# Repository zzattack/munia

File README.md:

MUNIA is a device that acquires input packets from controllers of various videogame consoles and shows them on your PC with the controller simultaneously remaining attached to its console. This allows you to display your inputs on gameplay videos or livestream content.
Devices for several consoles have been developed under this project:
* Nintendo Gamecube
* Sony Playstation 2
* Nintendo 64
* Super Nintendo

# Repository overview
* The hardware folder contains schematics for the various devices developed under this project. These include input adapters for Nintendo Gamecube, Nintendo 64, Super Nintendo, Sony PlayStation 2 and hybrids of the aforementioned.
* The firmware folder contains firmware projects for each of the circuit boards presented in the hardware folder.
* The munia.io folder contains the Django project powering the http://munia.io website (not functional).
* The MUNIA-win folder contains the .NET project 

## FAQ
Q. I don’t like the default skins, can I change them?
Absolutely. The software has a very strong SVG based theming engine. You can create a new one using tools like Adobe Illustrator or Inkscape. Custom XML attributes are used to map buttons to graphical elements. It’s pretty simple, honestly; take a look in SKINS.md!

Q. What does ‘MUNIA’ mean?
The very first iteration of the device supported SNES, N64 and NGC simultaneously. The acronym stands for ‘Multi-use Nintendo Input Adapter’. Both the Multi-use and Nintendo parts no longer apply to most of our devices, so we’ve parted with the acronym but kept the pretty name.

Q. Will you support console ‘X’?
Unless mentioned on the index page, the likely answer is no. Newer generation consoles are usually too complicated. The low expected demand for adapters for older generation consoles doesn’t warrant the required development investments at the moment.

Q. How does this compare to an Arduino input display?
Favorably. Benefits include not having to splice any cables, the device showing up as HID device on your computer, superior software, more stable firmware, ability to use the controller on our PC in e.g. emulators and better 3rd party controller support. In the end, though, both work and the MUNIA software also supports inputs from Arduino-based NintendoSpy devices!

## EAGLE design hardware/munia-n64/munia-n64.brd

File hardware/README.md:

# This folder contains the EAGLE schematics for the various hardware boards.

## munia
This contains schematics and board layout for the 3-in-1 device with support for the Nintendo Gamecube, Nintendo 64 and Super Nintendo/SFC consoles.
The enclosure also makes use of the 

## munia-ngc
This is the simplified Gamecube-only version of the device

## munia-n64
This is the simplified N64-only version of the device

## munia-snes
This is the simplified SNES-only version of the device

## musia
This is the Sony PS2 version

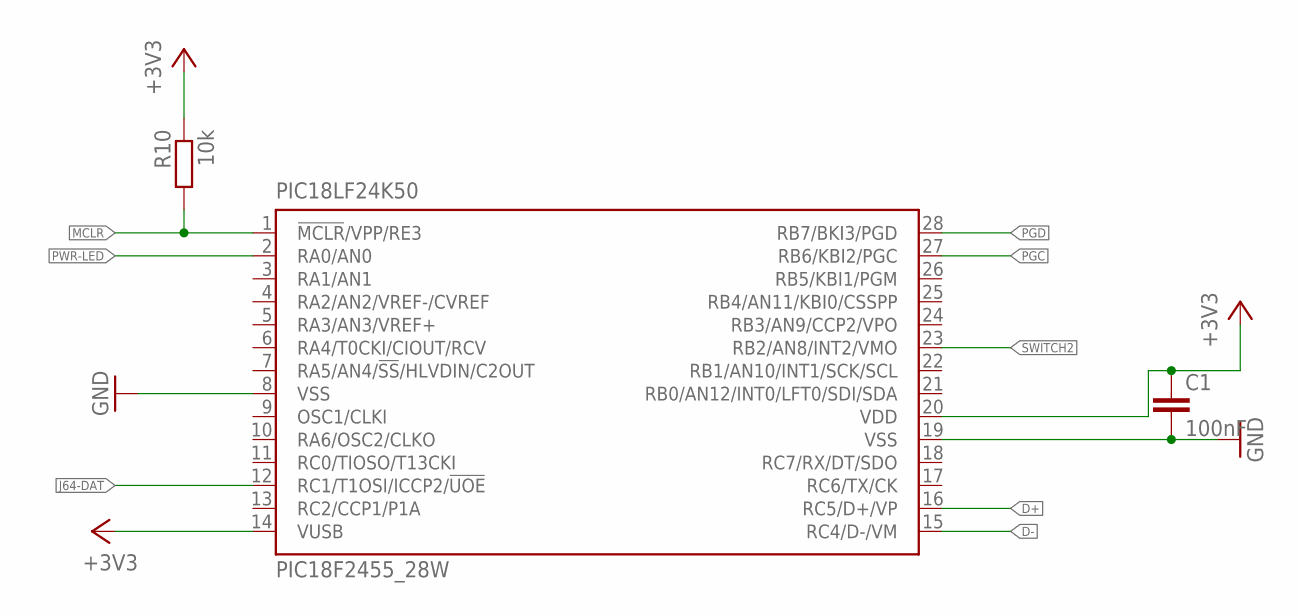
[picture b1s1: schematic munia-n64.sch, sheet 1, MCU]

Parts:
C1: 100nF; C0603
PIC18LF24K50: PIC18F2455_28W; SO28W
R10: 10k; R0603

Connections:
+3V3: C1.1, PIC18LF24K50.14 (VUSB), PIC18LF24K50.20 (VDD), R10.1; also elsewhere on the board
D+: PIC18LF24K50.16 (RC5/D+/VP); also elsewhere on the board
D-: PIC18LF24K50.15 (RC4/D-/VM); also elsewhere on the board
GND: C1.2, PIC18LF24K50.8 (VSS), PIC18LF24K50.19 (VSS); also elsewhere on the board
J64-DAT: PIC18LF24K50.12 (RC1/T1OSI/ICCP2/!UOE); also elsewhere on the board
MCLR: PIC18LF24K50.1 (!MCLR!/VPP/RE3), R10.2; also elsewhere on the board
PGC: PIC18LF24K50.27 (RB6/KBI2/PGC); also elsewhere on the board
PGD: PIC18LF24K50.28 (RB7/BKI3/PGD); also elsewhere on the board
PWR-LED: PIC18LF24K50.2 (RA0/AN0); also elsewhere on the board
SWITCH2: PIC18LF24K50.23 (RB2/AN8/INT2/VMO)

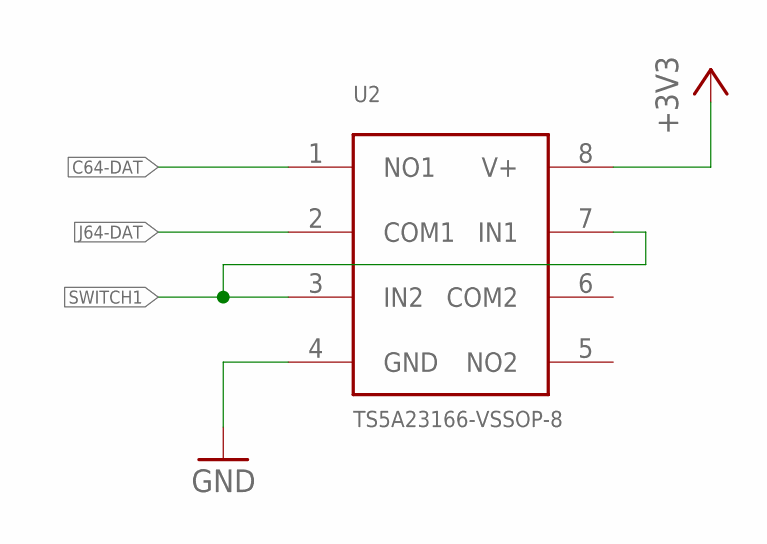
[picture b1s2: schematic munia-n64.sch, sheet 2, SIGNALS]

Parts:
U2: TS5A23166-VSSOP-8; SOT765

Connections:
+3V3: U2.8 (V+); also elsewhere on the board
C64-DAT: U2.1 (NO1); also elsewhere on the board
GND: U2.4 (GND); also elsewhere on the board
J64-DAT: U2.2 (COM1); also elsewhere on the board
SWITCH1: U2.3 (IN2), U2.7 (IN1)

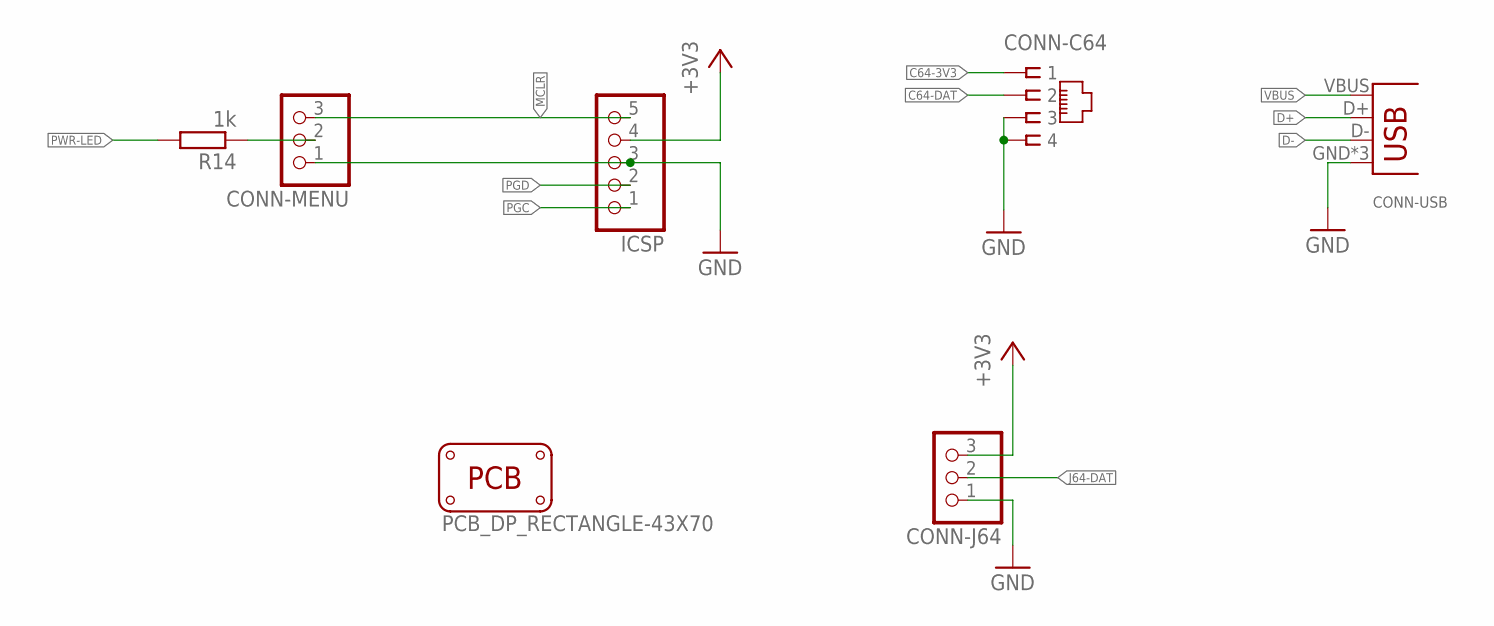
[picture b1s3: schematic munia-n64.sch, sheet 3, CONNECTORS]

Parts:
CONN-C64: RJ11-6P4C; RJ11-4C
CONN-J64: PINHD-1X3; 1X03
CONN-MENU: PINHD-1X3; 1X03
CONN-USB: USB-B-NIELS; USB-B-H
ICSP: PINHD-1X5; 1X05
PCB1: PCB_DP_RECTANGLE-43X70; DP7043_V1
R14: 1k; R0603

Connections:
+3V3: CONN-J64.3, ICSP.4; also elsewhere on the board
C64-3V3: CONN-C64.1; also elsewhere on the board
C64-DAT: CONN-C64.2; also elsewhere on the board
D+: CONN-USB.D+; also elsewhere on the board
D-: CONN-USB.D-; also elsewhere on the board
GND: CONN-C64.3, CONN-C64.4, CONN-J64.1, CONN-MENU.1, CONN-USB.GND, CONN-USB.GND@1 (GND), CONN-USB.GND@2 (GND), ICSP.3; also elsewhere on the board
J64-DAT: CONN-J64.2; also elsewhere on the board
MCLR: CONN-MENU.3, ICSP.5; also elsewhere on the board
unnamed: CONN-MENU.2, R14.1
PGC: ICSP.1; also elsewhere on the board
PGD: ICSP.2; also elsewhere on the board
PWR-LED: R14.2; also elsewhere on the board
VBUS: CONN-USB.VBUS; also elsewhere on the board

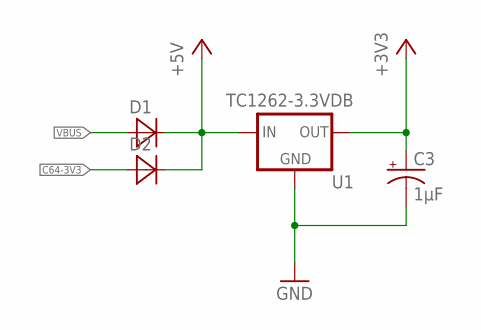
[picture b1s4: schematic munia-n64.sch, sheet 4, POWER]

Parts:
C3: 1µF; EIA3216
D1, D2: MBR120VLSFT1G; SOD123
U1: TC1262-3.3VDB; SOT230P700X180-4N

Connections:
+3V3: C3.A (+), U1.3 (OUT); also elsewhere on the board
+5V: D1.1 (C), D2.1 (C), U1.1 (IN)
C64-3V3: D2.2 (A); also elsewhere on the board
GND: C3.C (-), U1.2 (GND), U1.4 (GND); also elsewhere on the board
VBUS: D1.2 (A); also elsewhere on the board

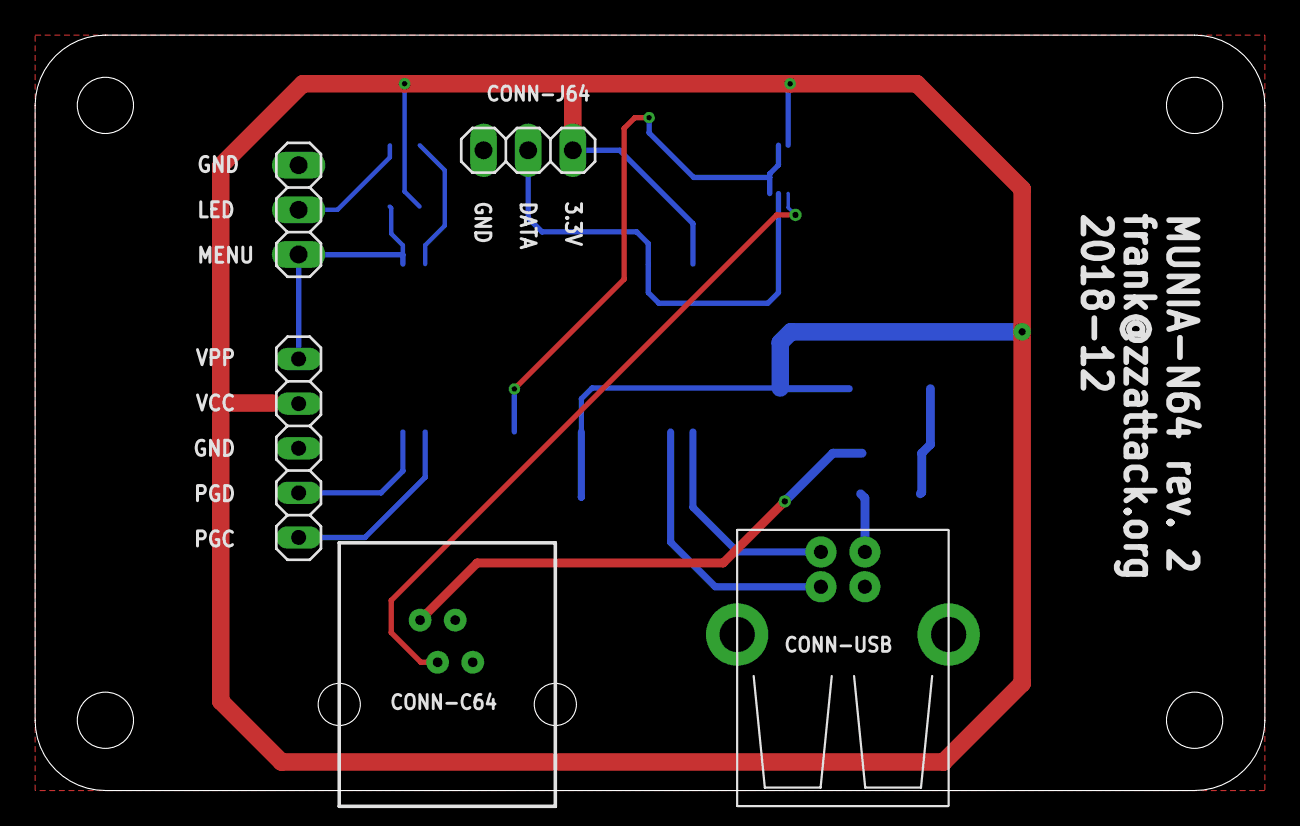
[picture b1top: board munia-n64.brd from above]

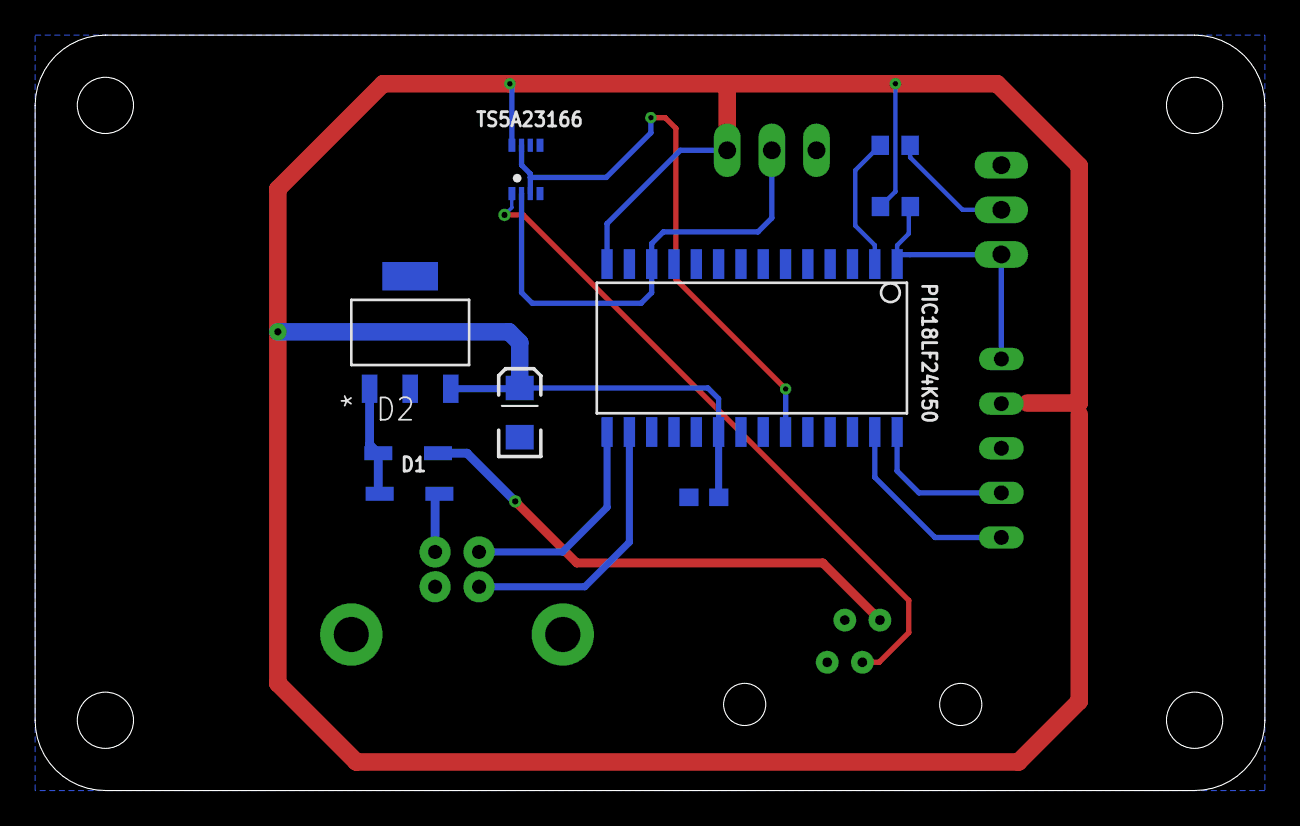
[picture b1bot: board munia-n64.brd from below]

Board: 2 copper layers, 70.0 x 43.0 mm, 15 parts (9 on the bottom side), 15 nets.

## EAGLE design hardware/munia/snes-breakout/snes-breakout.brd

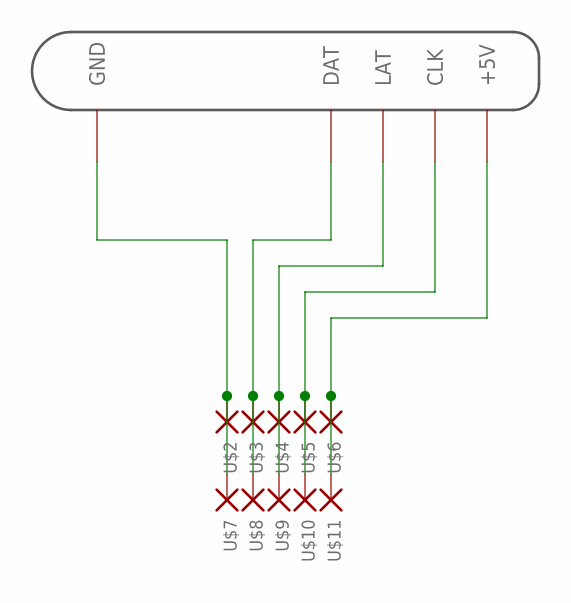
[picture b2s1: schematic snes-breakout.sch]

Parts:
U$1: SNES-CONNECTOR
U$2, U$3, U$4, U$5, U$6, U$7, U$8, U$9, U$10, U$11: SMDPADSMD6080; SMD6080

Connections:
CLK: U$1.P$6 (CLK), U$5.P$1, U$10.P$1
DAT: U$1.P$4 (DAT), U$3.P$1, U$8.P$1
GND: U$1.P$1 (GND), U$2.P$1, U$7.P$1
LAT: U$1.P$5 (LAT), U$4.P$1, U$9.P$1
VCC: U$1.P$7 (+5V), U$6.P$1, U$11.P$1

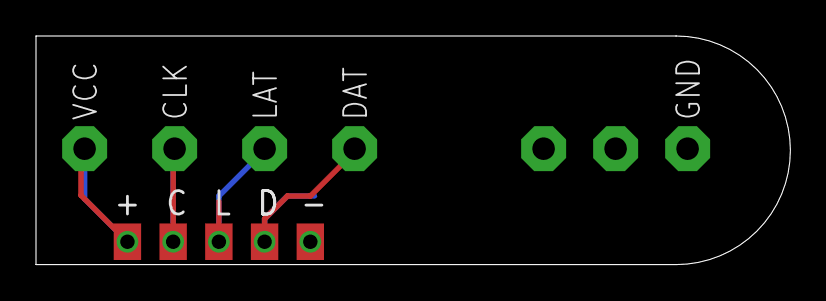
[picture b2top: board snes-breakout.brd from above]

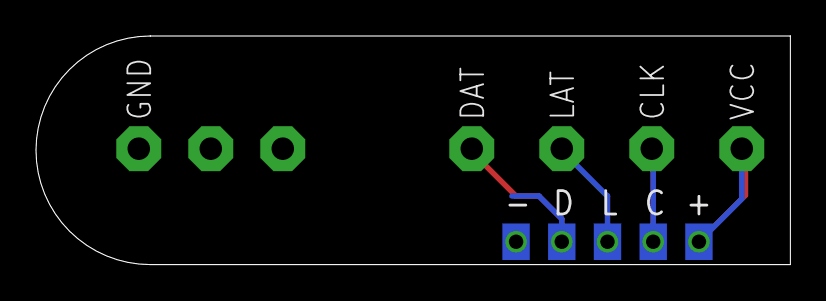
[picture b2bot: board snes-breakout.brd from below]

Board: 2 copper layers, 41.9 x 12.7 mm, 11 parts (5 on the bottom side), 5 nets.

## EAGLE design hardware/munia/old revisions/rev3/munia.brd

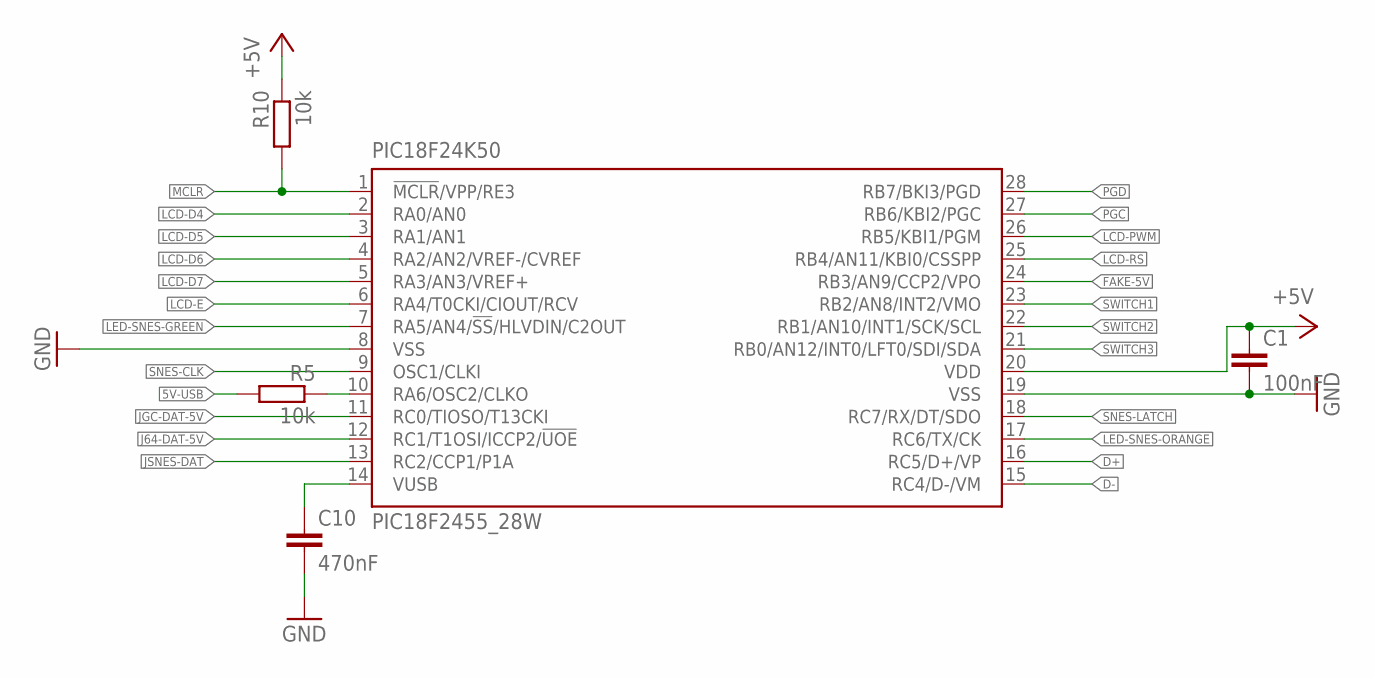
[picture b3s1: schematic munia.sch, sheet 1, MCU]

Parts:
C1: 100nF; C0603
C10: 470nF; C0603
PIC18F24K50: PIC18F2455_28W; SO28W
R5, R10: 10k; R0603

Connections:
5V-USB: R5.2; also elsewhere on the board
+5V: C1.1, PIC18F24K50.20 (VDD), R10.1; also elsewhere on the board
D+: PIC18F24K50.16 (RC5/D+/VP); also elsewhere on the board
D-: PIC18F24K50.15 (RC4/D-/VM); also elsewhere on the board
FAKE-5V: PIC18F24K50.24 (RB3/AN9/CCP2/VPO); also elsewhere on the board
GND: C1.2, C10.2, PIC18F24K50.8 (VSS), PIC18F24K50.19 (VSS); also elsewhere on the board
J64-DAT-5V: PIC18F24K50.12 (RC1/T1OSI/ICCP2/!UOE); also elsewhere on the board
JGC-DAT-5V: PIC18F24K50.11 (RC0/TIOSO/T13CKI); also elsewhere on the board
JSNES-DAT: PIC18F24K50.13 (RC2/CCP1/P1A); also elsewhere on the board
LCD-D4: PIC18F24K50.2 (RA0/AN0); also elsewhere on the board
LCD-D5: PIC18F24K50.3 (RA1/AN1); also elsewhere on the board
LCD-D6: PIC18F24K50.4 (RA2/AN2/VREF-/CVREF); also elsewhere on the board
LCD-D7: PIC18F24K50.5 (RA3/AN3/VREF+); also elsewhere on the board
LCD-E: PIC18F24K50.6 (RA4/T0CKI/CIOUT/RCV); also elsewhere on the board
LCD-PWM: PIC18F24K50.26 (RB5/KBI1/PGM); also elsewhere on the board
LCD-RS: PIC18F24K50.25 (RB4/AN11/KBI0/CSSPP); also elsewhere on the board
LED-SNES-GREEN: PIC18F24K50.7 (RA5/AN4/!SS!/HLVDIN/C2OUT); also elsewhere on the board
LED-SNES-ORANGE: PIC18F24K50.17 (RC6/TX/CK); also elsewhere on the board
MCLR: PIC18F24K50.1 (!MCLR!/VPP/RE3), R10.2; also elsewhere on the board
unnamed: C10.1, PIC18F24K50.14 (VUSB)
PGC: PIC18F24K50.27 (RB6/KBI2/PGC); also elsewhere on the board
PGD: PIC18F24K50.28 (RB7/BKI3/PGD); also elsewhere on the board
SNES-CLK: PIC18F24K50.9 (OSC1/CLKI); also elsewhere on the board
SNES-LATCH: PIC18F24K50.18 (RC7/RX/DT/SDO); also elsewhere on the board
SWITCH1: PIC18F24K50.23 (RB2/AN8/INT2/VMO); also elsewhere on the board
SWITCH2: PIC18F24K50.22 (RB1/AN10/INT1/SCK/SCL); also elsewhere on the board
SWITCH3: PIC18F24K50.21 (RB0/AN12/INT0/LFT0/SDI/SDA); also elsewhere on the board
USB-SENSE: PIC18F24K50.10 (RA6/OSC2/CLKO), R5.1

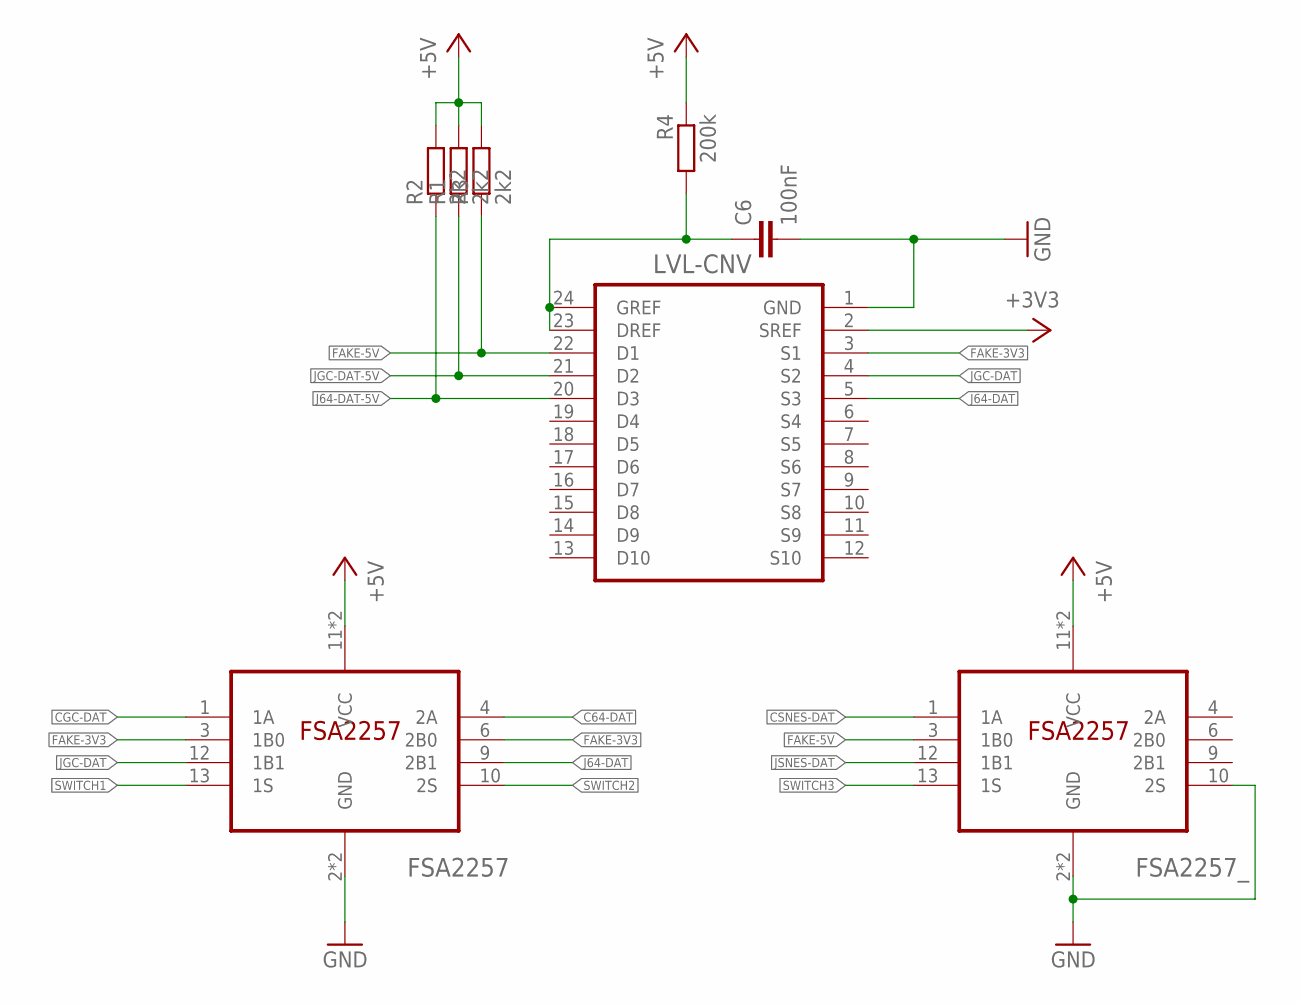
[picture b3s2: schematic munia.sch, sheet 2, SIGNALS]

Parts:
C6: 100nF; C0603
FSA2257, FSA2257_: FSA2257MTCX; TSSOP14
LVL-CNV: GTL2010; TSSOP24
R1, R2, R3: 2k2; R0603
R4: 200k; R0603

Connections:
+3V3: LVL-CNV.2 (SREF); also elsewhere on the board
+5V: FSA2257.11 (VCC), FSA2257.14 (VCC), FSA2257_.11 (VCC), FSA2257_.14 (VCC), R1.2, R2.2, R3.2, R4.1; also elsewhere on the board
C64-DAT: FSA2257.4 (2A); also elsewhere on the board
CGC-DAT: FSA2257.1 (1A); also elsewhere on the board
CSNES-DAT: FSA2257_.1 (1A); also elsewhere on the board
FAKE-3V3: FSA2257.3 (1B0), FSA2257.6 (2B0), LVL-CNV.3 (S1)
FAKE-5V: FSA2257_.3 (1B0), LVL-CNV.22 (D1), R3.1; also elsewhere on the board
GND: C6.2, FSA2257.2 (GND), FSA2257.5 (GND), FSA2257_.2 (GND), FSA2257_.5 (GND), FSA2257_.10 (2S), LVL-CNV.1 (GND); also elsewhere on the board
J64-DAT: FSA2257.9 (2B1), LVL-CNV.5 (S3); also elsewhere on the board
J64-DAT-5V: LVL-CNV.20 (D3), R2.1; also elsewhere on the board
JGC-DAT: FSA2257.12 (1B1), LVL-CNV.4 (S2); also elsewhere on the board
JGC-DAT-5V: LVL-CNV.21 (D2), R1.1; also elsewhere on the board
JSNES-DAT: FSA2257_.12 (1B1); also elsewhere on the board
unnamed: C6.1, LVL-CNV.23 (DREF), LVL-CNV.24 (GREF), R4.2
SWITCH1: FSA2257.13 (1S); also elsewhere on the board
SWITCH2: FSA2257.10 (2S); also elsewhere on the board
SWITCH3: FSA2257_.13 (1S); also elsewhere on the board

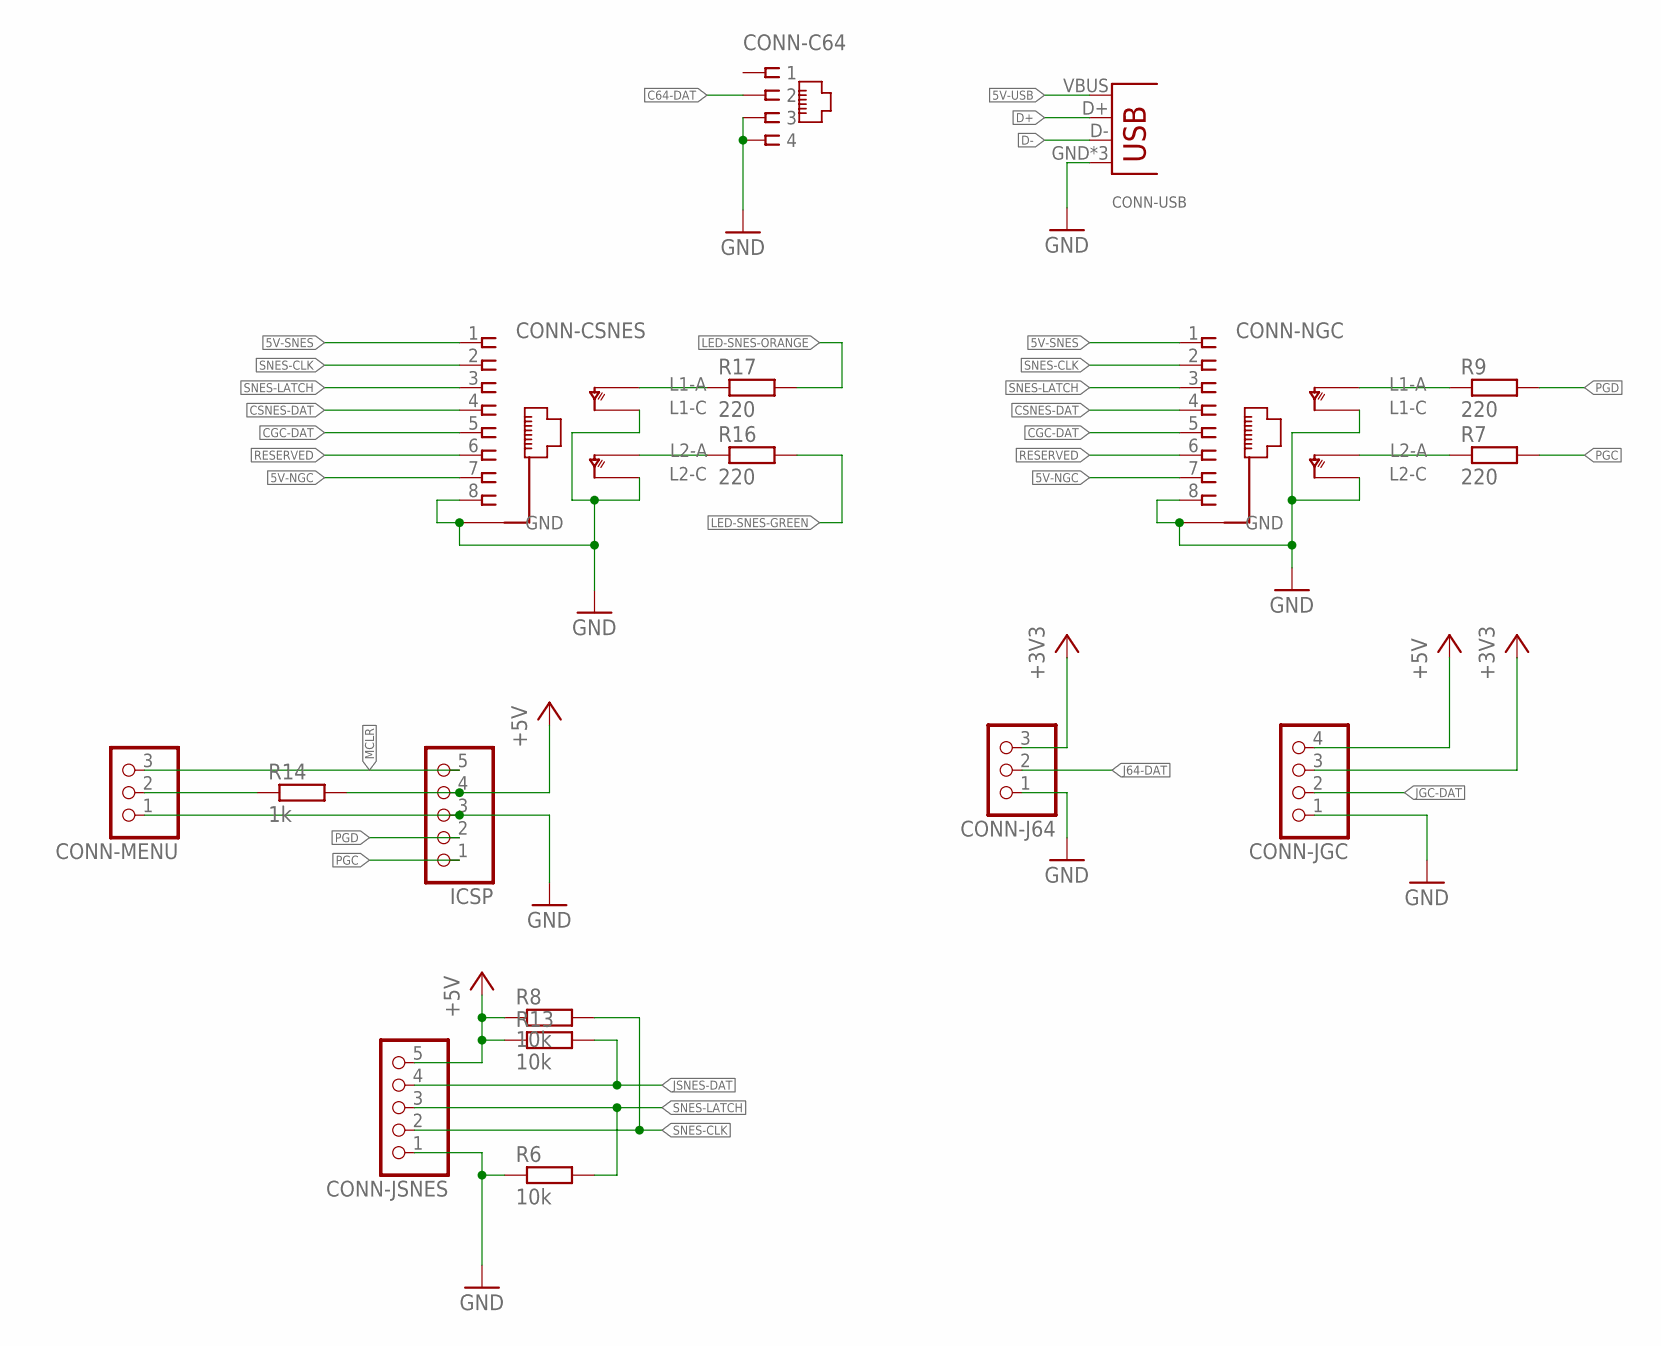
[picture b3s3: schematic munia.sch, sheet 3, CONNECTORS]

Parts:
CONN-C64: RJ11-6P4C; RJ11-4C
CONN-CSNES: RJ45-NIELS
CONN-J64: PINHD-1X3; 1X03
CONN-JGC: PINHD-1X4; 1X04
CONN-JSNES: PINHD-1X5; 1X05
CONN-MENU: PINHD-1X3; 1X03
CONN-NGC: RJ45-NIELS
CONN-USB: USB-B-NIELS; USB-B-H
ICSP: PINHD-1X5; 1X05
R6, R8, R13: 10k; R0603
R7, R9, R16, R17: 220; R0603
R14: 1k; R0603

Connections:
5V-NGC: CONN-CSNES.7, CONN-NGC.7; also elsewhere on the board
5V-SNES: CONN-CSNES.1, CONN-NGC.1; also elsewhere on the board
5V-USB: CONN-USB.VBUS; also elsewhere on the board
+3V3: CONN-J64.3, CONN-JGC.3; also elsewhere on the board
+5V: CONN-JGC.4, CONN-JSNES.5, ICSP.4, R8.1, R13.1, R14.2; also elsewhere on the board
C64-DAT: CONN-C64.2; also elsewhere on the board
CGC-DAT: CONN-CSNES.5, CONN-NGC.5; also elsewhere on the board
CSNES-DAT: CONN-CSNES.4, CONN-NGC.4; also elsewhere on the board
D+: CONN-USB.D+; also elsewhere on the board
D-: CONN-USB.D-; also elsewhere on the board
GND: CONN-C64.3, CONN-C64.4, CONN-CSNES.8, CONN-CSNES.GND@5 (GND), CONN-CSNES.GND@6 (GND), CONN-CSNES.LED-GREEN-C (L2C), CONN-CSNES.LED-ORANGE-C (L1C), CONN-J64.1, CONN-JGC.1, CONN-JSNES.1, CONN-MENU.1, CONN-NGC.8, CONN-NGC.GND@5 (GND), CONN-NGC.GND@6 (GND), CONN-NGC.LED-GREEN-C (L2C), CONN-NGC.LED-ORANGE-C (L1C), CONN-USB.GND, CONN-USB.GND@1 (GND), CONN-USB.GND@2 (GND), ICSP.3, R6.1; also elsewhere on the board
J64-DAT: CONN-J64.2; also elsewhere on the board
JGC-DAT: CONN-JGC.2; also elsewhere on the board
JSNES-DAT: CONN-JSNES.4, R13.2; also elsewhere on the board
LED-SNES-GREEN: R16.2; also elsewhere on the board
LED-SNES-ORANGE: R17.2; also elsewhere on the board
MCLR: CONN-MENU.3, ICSP.5; also elsewhere on the board
unnamed: CONN-CSNES.LED-ORANGE-A (L1A), R17.1
unnamed: CONN-CSNES.LED-GREEN-A (L2A), R16.1
unnamed: CONN-NGC.LED-ORANGE-A (L1A), R9.1
unnamed: CONN-NGC.LED-GREEN-A (L2A), R7.1
PGC: ICSP.1, R7.2; also elsewhere on the board
PGD: ICSP.2, R9.2; also elsewhere on the board
PWR-LED: CONN-MENU.2, R14.1
RESERVED: CONN-CSNES.6, CONN-NGC.6
SNES-CLK: CONN-CSNES.2, CONN-JSNES.2, CONN-NGC.2, R8.2; also elsewhere on the board
SNES-LATCH: CONN-CSNES.3, CONN-JSNES.3, CONN-NGC.3, R6.2; also elsewhere on the board

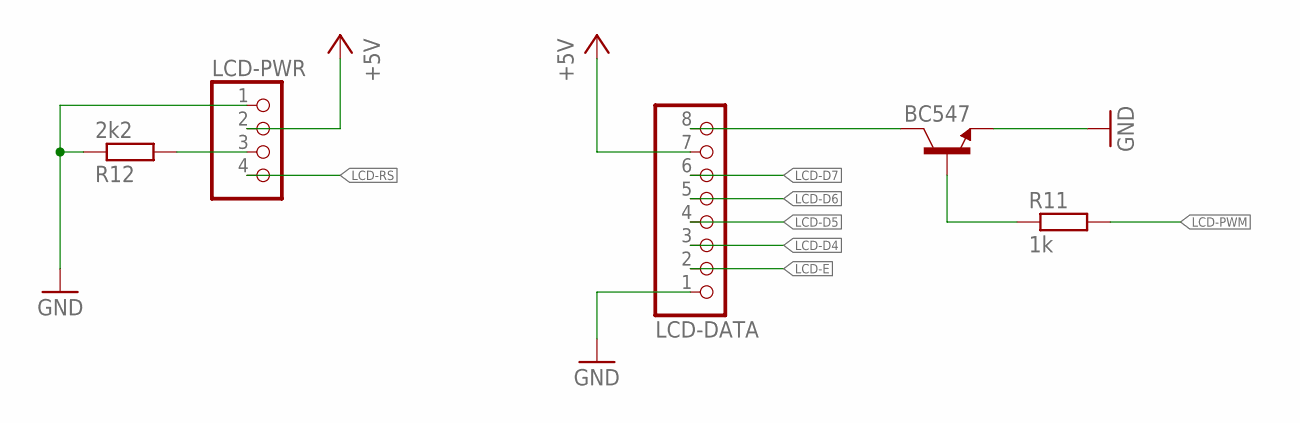
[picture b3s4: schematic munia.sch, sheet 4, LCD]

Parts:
BC547: BC847; SOT23
LCD-DATA: PINHD-1X8; 1X08
LCD-PWR: PINHD-1X4; 1X04
R11: 1k; R0603
R12: 2k2; R0603

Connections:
+5V: LCD-DATA.7, LCD-PWR.2; also elsewhere on the board
C: BC547.3 (C), LCD-DATA.8
GND: BC547.2 (E), LCD-DATA.1, LCD-PWR.1, R12.1; also elsewhere on the board
LCD-D4: LCD-DATA.3; also elsewhere on the board
LCD-D5: LCD-DATA.4; also elsewhere on the board
LCD-D6: LCD-DATA.5; also elsewhere on the board
LCD-D7: LCD-DATA.6; also elsewhere on the board
LCD-E: LCD-DATA.2; also elsewhere on the board
LCD-PWM: R11.2; also elsewhere on the board
LCD-RS: LCD-PWR.4; also elsewhere on the board
unnamed: BC547.1 (B), R11.1
VEE: LCD-PWR.3, R12.2

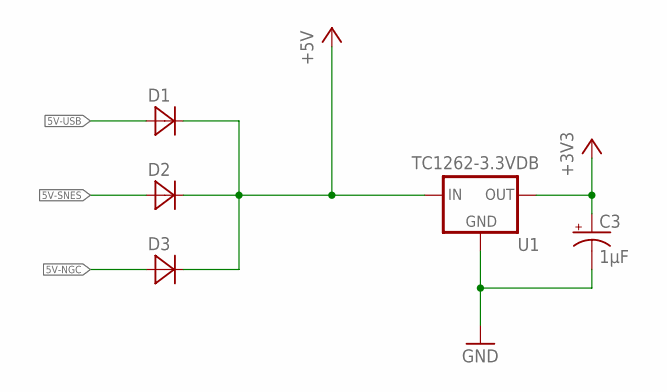
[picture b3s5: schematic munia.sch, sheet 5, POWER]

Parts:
C3: 1µF; EIA3216
D1, D2, D3: MBR120VLSFT1G; SOD123
U1: TC1262-3.3VDB; SOT230P700X180-4N

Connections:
5V-NGC: D3.2 (A); also elsewhere on the board
5V-SNES: D2.2 (A); also elsewhere on the board
5V-USB: D1.2 (A); also elsewhere on the board
+3V3: C3.A (+), U1.3 (OUT); also elsewhere on the board
+5V: D1.1 (C), D2.1 (C), D3.1 (C), U1.1 (IN); also elsewhere on the board
GND: C3.C (-), U1.2 (GND), U1.4 (GND); also elsewhere on the board

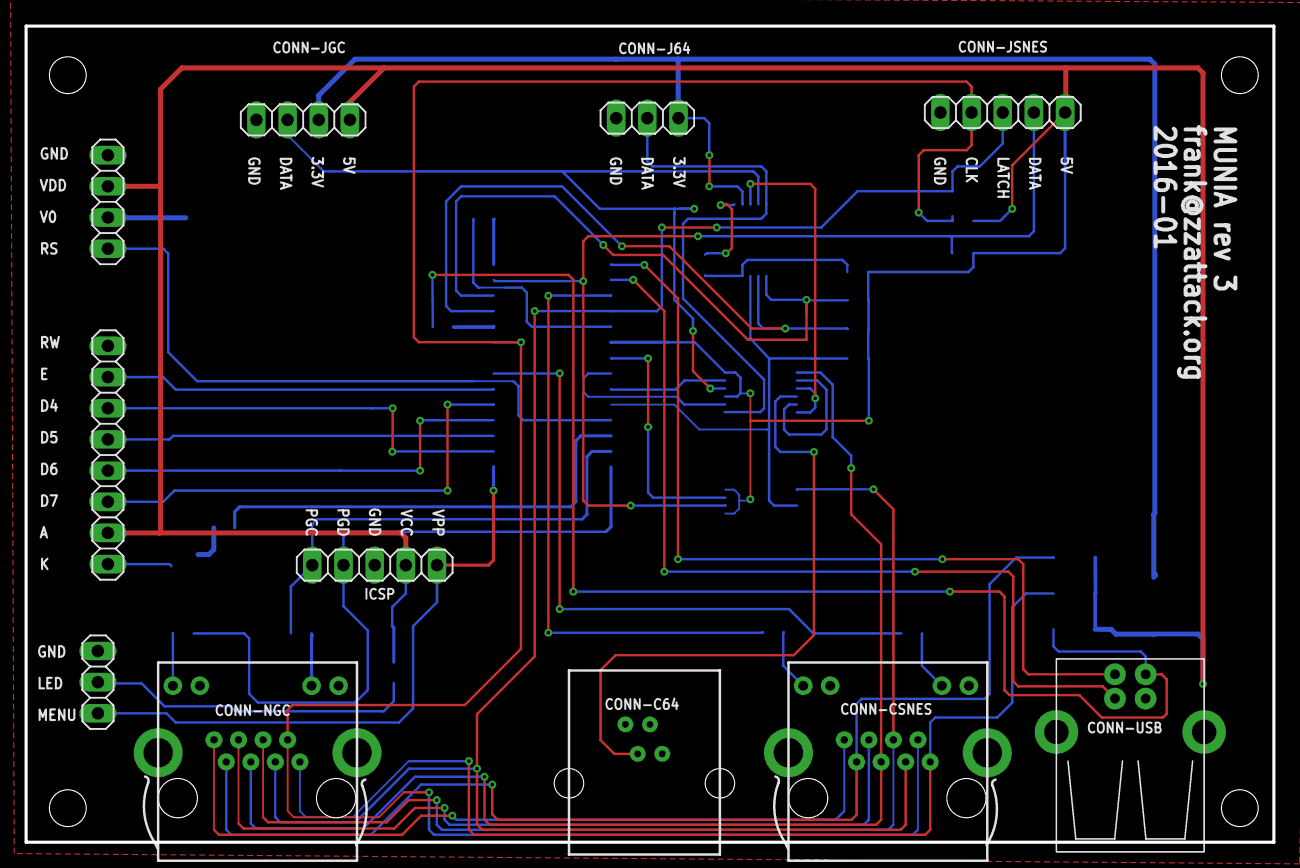
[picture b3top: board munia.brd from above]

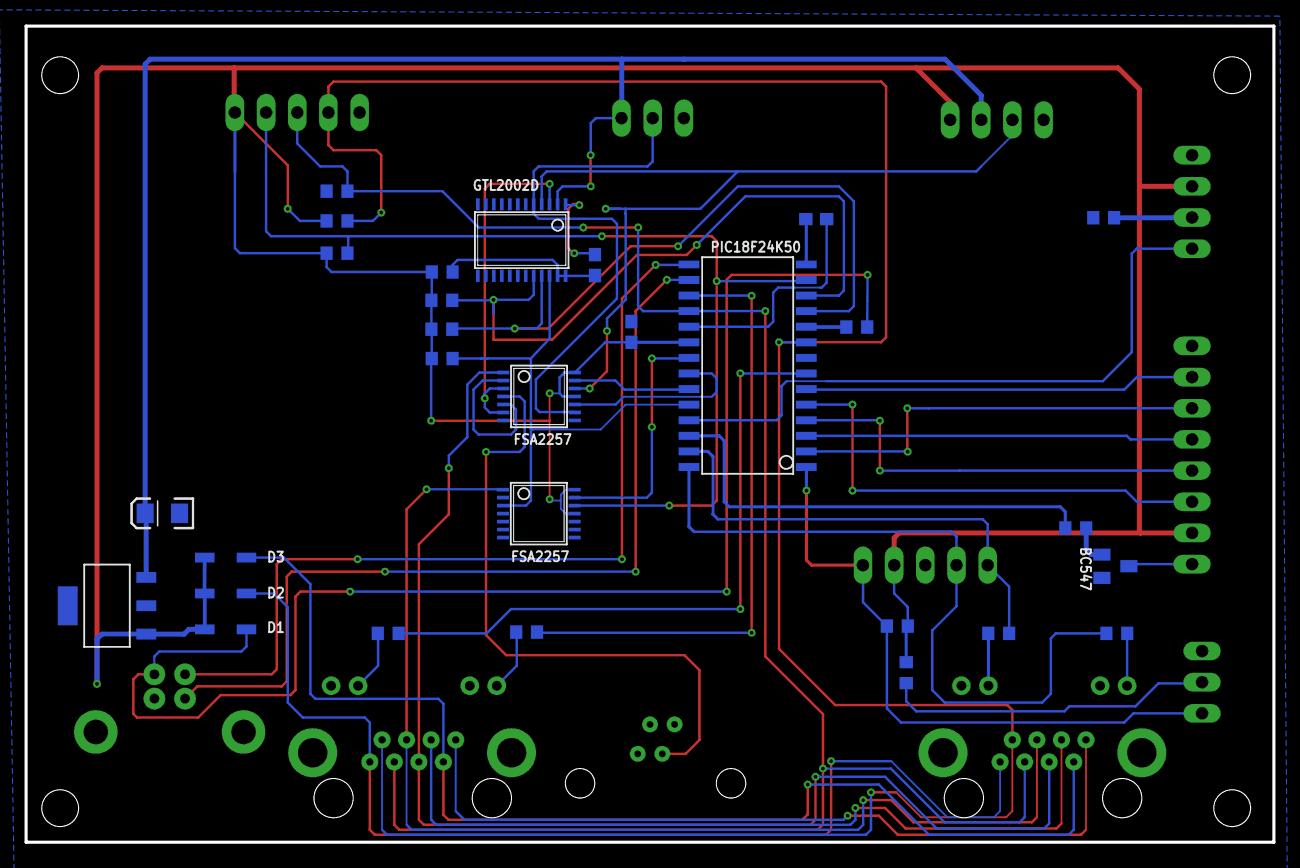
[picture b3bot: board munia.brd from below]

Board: 2 copper layers, 101.7 x 66.5 mm, 40 parts (29 on the bottom side), 47 nets.

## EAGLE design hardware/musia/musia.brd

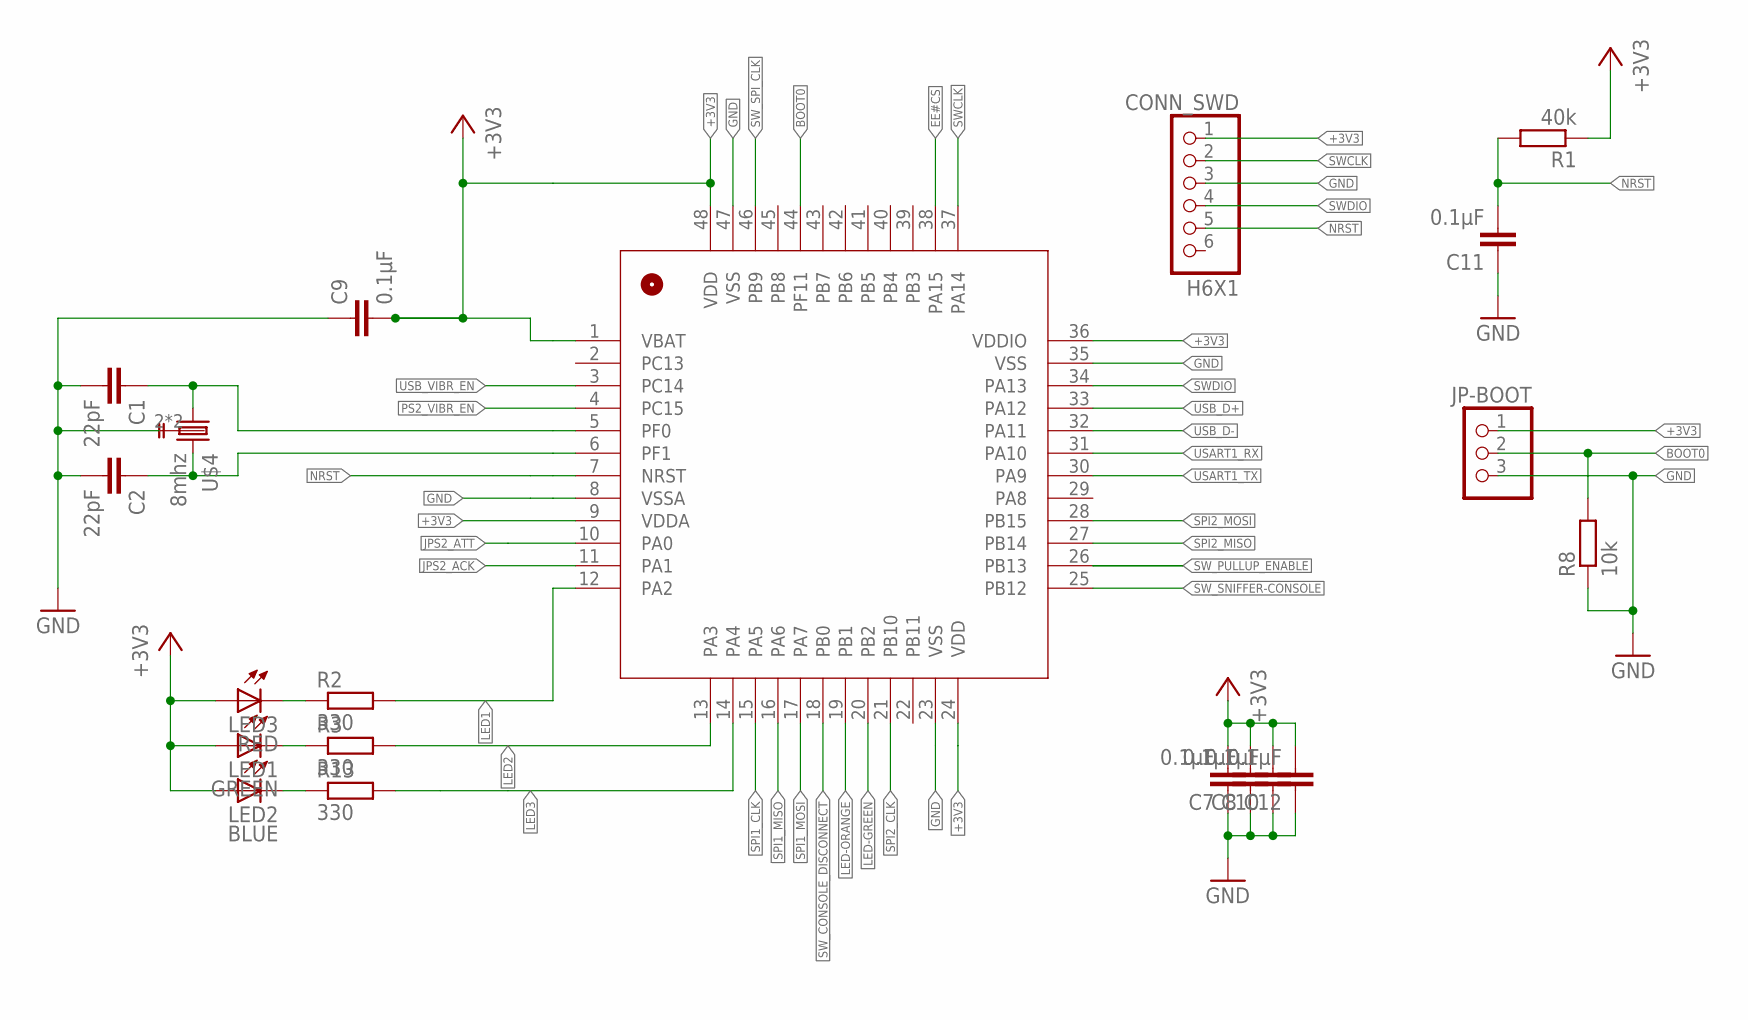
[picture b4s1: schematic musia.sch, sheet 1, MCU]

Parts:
C1, C2: 22pF; C0603
C7, C8, C9, C10, C11, C12: 0.1µF; C0603
CONN_SWD: H6X1; 1X06
JP-BOOT: PINHD-1X3; 1X03
LED1: GREEN; CHIPLED_0805
LED2: BLUE; CHIPLED_0805
LED3: RED; CHIPLED_0805
R1: 40k; R0603
R2, R3, R13: 330; R0603
R8: 10k; R0603
U$1: STM32F0425; LQFP48-STM32
U$4: 8mhz; ABM3B

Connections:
+3V3: C7.2, C8.2, C9.2, C10.2, C12.2, CONN_SWD.1, JP-BOOT.1, LED1.A, LED2.A, LED3.A, R1.1, U$1.1 (VBAT), U$1.9 (VDDA), U$1.24 (VDD), U$1.36 (VDDIO), U$1.48 (VDD); also elsewhere on the board
BOOT0: JP-BOOT.2, R8.2, U$1.44 (PF11)
EE#CS: U$1.38 (PA15); also elsewhere on the board
GND: C1.2, C2.2, C7.1, C8.1, C9.1, C10.1, C11.1, C12.1, CONN_SWD.3, JP-BOOT.3, R8.1, U$1.8 (VSSA), U$1.23 (VSS), U$1.35 (VSS), U$1.47 (VSS), U$4.2 (GND), U$4.4 (GND); also elsewhere on the board
JPS2_ACK: U$1.11 (PA1); also elsewhere on the board
JPS2_ATT: U$1.10 (PA0); also elsewhere on the board
LED1: R2.2, U$1.12 (PA2)
LED2: R3.2, U$1.13 (PA3)
LED3: R13.2, U$1.14 (PA4)
LED-GREEN: U$1.20 (PB2); also elsewhere on the board
LED-ORANGE: U$1.19 (PB1); also elsewhere on the board
unnamed: LED3.C, R2.1
unnamed: LED2.C, R13.1
unnamed: LED1.C, R3.1
unnamed: C2.1, U$1.6 (PF1), U$4.3 (2)
unnamed: C1.1, U$1.5 (PF0), U$4.1
NRST: C11.2, CONN_SWD.5, R1.2, U$1.7 (NRST)
PS2_VIBR_EN: U$1.4 (PC15); also elsewhere on the board
SPI1_CLK: U$1.15 (PA5); also elsewhere on the board
SPI1_MISO: U$1.16 (PA6); also elsewhere on the board
SPI1_MOSI: U$1.17 (PA7); also elsewhere on the board
SPI2_CLK: U$1.21 (PB10); also elsewhere on the board
SPI2_MISO: U$1.27 (PB14); also elsewhere on the board
SPI2_MOSI: U$1.28 (PB15); also elsewhere on the board
SWCLK: CONN_SWD.2, U$1.37 (PA14)
SWDIO: CONN_SWD.4, U$1.34 (PA13)
SW_CONSOLE_DISCONNECT: U$1.18 (PB0); also elsewhere on the board
SW_PULLUP_ENABLE: U$1.26 (PB13); also elsewhere on the board
SW_SNIFFER-CONSOLE: U$1.25 (PB12); also elsewhere on the board
SW_SPI_CLK: U$1.46 (PB9); also elsewhere on the board
USART1_RX: U$1.31 (PA10); also elsewhere on the board
USART1_TX: U$1.30 (PA9); also elsewhere on the board
USB_D+: U$1.33 (PA12); also elsewhere on the board
USB_D-: U$1.32 (PA11); also elsewhere on the board
USB_VIBR_EN: U$1.3 (PC14); also elsewhere on the board

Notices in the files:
hardware/munia/ngc-breakout/ngc-breakout.brd:
(c) 2016 MUNIA.io
parts and their libraries:
SparkFun-Capacitors: Licensing: Creative Commons ShareAlike 4.0 International - https://creativecommons.org/licenses/by-sa/4.0
